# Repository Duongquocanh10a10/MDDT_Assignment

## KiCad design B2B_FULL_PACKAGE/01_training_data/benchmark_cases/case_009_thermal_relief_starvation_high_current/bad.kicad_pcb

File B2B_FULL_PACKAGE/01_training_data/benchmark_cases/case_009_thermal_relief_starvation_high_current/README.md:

# Benchmark Case: case_009_thermal_relief_starvation_high_current

## Title
High-Current Boost Inductor Pad Thermal Relief Starvation

## Category
`thermal_spoke_starvation` (IPC-2221 & IPC-7351 Standards)

## Engineering Description & Root Cause
MT3608 2.2A inductor switching node pad was connected to copper zone via only 1 of 4 spokes due to routing corridor choke, violating IPC-2221 current carrying capacity (0.8A max per spoke). Transformation reorients escape vias to restore all 4 0.40mm thermal spokes.

## Verification Metrics
- **Initial DRC Violations:** 2
- **Post-Transformation Violations:** 0 (100% Convergence Verified)
- **Signal Integrity Improvement:** Validated with open-source field solver models.

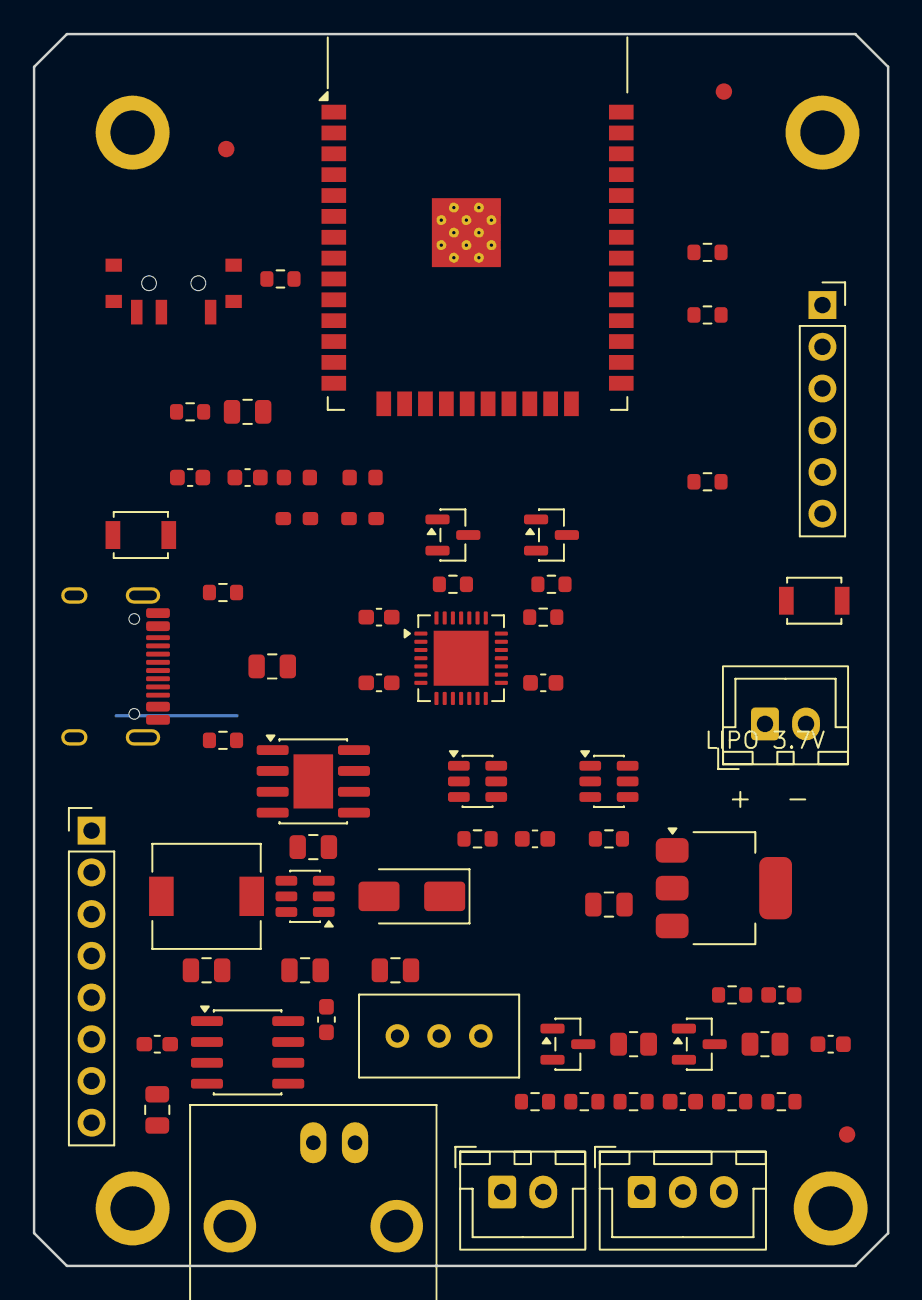
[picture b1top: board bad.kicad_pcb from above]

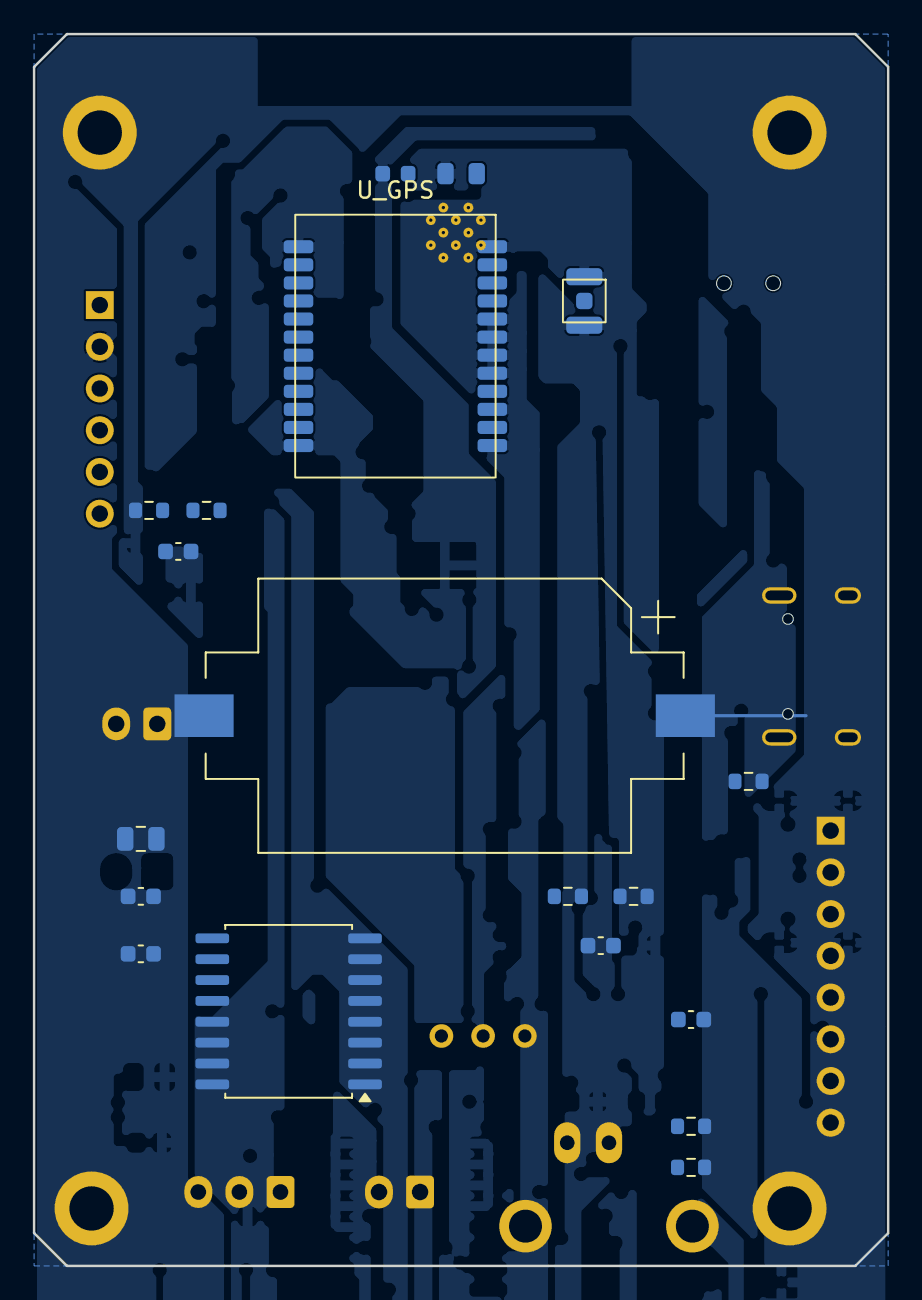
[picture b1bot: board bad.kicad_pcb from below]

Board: 4 copper layers, 52.0 x 75.0 mm, 94 parts (19 on the bottom side), 62 nets.

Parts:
BT1: CR2032; BatteryHolder_Keystone_1060_1x2032
C_ANA_BULK: 10uF; C_0805_2012Metric
C_BAT_ADC: 100nF; C_0603_1608Metric
C_BAT_CHG: 10uF; C_0805_2012Metric
C_BST_IN: 22uF; C_0805_2012Metric
C_BST_OUT1, C_BST_OUT2: 22uF; C_0805_2012Metric
C_CP_DEC: 100nF; C_0603_1608Metric
C_CP_VDD: 4.7uF; C_0603_1608Metric
C_CP_VREG: 4.7uF; C_0603_1608Metric
C_DS_VCC: 100nF; C_0603_1608Metric
C_EN: 100nF; C_0603_1608Metric
C_FF: 22pF; C_0603_1608Metric
C_GPS1: 100nF; C_0603_1608Metric
C_GPS2: 10uF; C_0805_2012Metric
C_LCD_VCC: 100nF; C_0603_1608Metric
C_LDO_DEC: 100nF; C_0603_1608Metric
C_LDO_IN: 10uF; C_0805_2012Metric
C_LDO_OUT: 22uF; C_0805_2012Metric
C_MCU_BULK: 10uF; C_0805_2012Metric
C_MCU_DEC: 100nF; C_0603_1608Metric
C_PH_FILT: 100nF; C_0603_1608Metric
C_RTC_VCC: 100nF; C_0603_1608Metric
C_TDS_FILT: 100nF; C_0603_1608Metric
C_U9_VCC: 100nF; C_0603_1608Metric
C_VBUS: 10uF; C_0805_2012Metric
C_VDD: 100nF; C_0603_1608Metric
D1: SS34; D_SMA
D_CHRG: CHRG; LED_0603_1608Metric
D_STDBY: STDBY; LED_0603_1608Metric
FB1: Ferrite_Bead; L_0603_1608Metric
FID1, FID2, FID3: FID; Fiducial_1mm_Mask2mm
H1, H2, H3, H4: M2.5; MountingHole_2.7mm_M2.5_Pad
J_ANT: U.FL; U.FL_Hirose_U.FL-R-SMT-1_Vertical
J_BAT: LIPO 3.7V; JST_XH_B2B-XH-A_1x02_P2.50mm_Vertical
J_BNC: BNC_pH; BNC_Amphenol_B6252HB-NPP3G-50_Horizontal
J_BOOT: BOOT/UART; PinHeader_1x06_P2.54mm_Vertical
J_LCD: TFT_LCD; PinHeader_1x08_P2.54mm_Vertical
J_TDS: TDS; JST_XH_B2B-XH-A_1x02_P2.50mm_Vertical
J_TEMP: DS18B20; JST_XH_B3B-XH-A_1x03_P2.50mm_Vertical
J_USB: USB-C; USB_C_Receptacle_HRO_TYPE-C-31-M-12
L1: 2.2uH; L_6.3x6.3_H3
Q1: 2N7002_TDS; SOT-23
Q2: 2N7002_LCD; SOT-23
Q3, Q4: MMBT3904; SOT-23
RV1: 10k_OFFSET; Potentiometer_Bourns_3296W_Vertical
R_BAT1, R_BAT2: 100k; R_0603_1608Metric
R_BL_LIM: 15R; R_0805_2012Metric
R_CC1, R_CC2: 5.1k; R_0603_1608Metric
R_CHRG: 1k; R_0603_1608Metric
R_CP_RST: 10k; R_0603_1608Metric
R_CS: 1k; R_0603_1608Metric
R_DS_PU: 4.7k; R_0603_1608Metric
R_DTR: 10k; R_0603_1608Metric
R_EN: 10k; R_0603_1608Metric
R_FB1: 22k; R_0603_1608Metric
R_FB2: 3.0k; R_0603_1608Metric
R_IO0: 10k; R_0603_1608Metric
R_LCD_GATE: 1k; R_0603_1608Metric
R_LCD_PD: 100k; R_0603_1608Metric
R_PH_BIAS: 10k; R_0603_1608Metric
R_PH_FILT: 1k; R_0603_1608Metric
R_PROG: 2.4k; R_0603_1608Metric
R_RTC_PU: 10k; R_0603_1608Metric
R_RTS: 10k; R_0603_1608Metric
R_SCL_PU: 4.7k; R_0603_1608Metric
R_SDA_PU: 4.7k; R_0603_1608Metric
R_STDBY: 1k; R_0603_1608Metric
R_TDS_FILT: 1k; R_0603_1608Metric
R_TDS_GATE: 1k; R_0603_1608Metric
R_TDS_PD: 100k; R_0603_1608Metric
R_TDS_REF: 1k_1%; R_0805_2012Metric
R_VDD: 100R; R_0603_1608Metric
SW1: ON/OFF; SW_SPDT_PCM12
SW_BOOT: BOOT; SW_SPST_B3U-1000P
SW_EN: RESET; SW_SPST_B3U-1000P
U1: TP4056; SOIC-8-1EP_3.9x4.9mm_P1.27mm_EP2.41x3.3mm
U2: DW01A; SOT-23-6
U3: FS8205A; SOT-23-6
U4: MT3608; SOT-23-6
U5: AMS1117; SOT-223-3_TabPin2
U6: ESP32; ESP32-WROOM-32
U7: DS3231; SOIC-16W_7.5x10.3mm_P1.27mm
U8: CP2102N; QFN-28-1EP_5x5mm_P0.5mm_EP3.35x3.35mm
U9: MCP6002; SOIC-8_3.9x4.9mm_P1.27mm
U_GPS: NEO-M8N; u-blox_NEO

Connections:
+3V3: C_DS_VCC.1, C_GPS1.1, C_GPS2.1, C_LCD_VCC.1, C_LDO_DEC.1, C_LDO_OUT.1, C_MCU_BULK.1, C_MCU_DEC.1, C_RTC_VCC.1, J_BOOT.1, J_LCD.2, J_TEMP.3, R_DS_PU.2, R_EN.2, R_IO0.2, R_RTC_PU.2, R_SCL_PU.2, R_SDA_PU.2, R_TDS_REF.2, U5.2, U6.2, U7.2, U_GPS.22, U_GPS.23
+5V: C_BST_OUT1.1, C_BST_OUT2.1, C_FF.1, C_LDO_IN.1, D1.1, FB1.1, R_FB1.1, U5.3
+5V_ANA: C_ANA_BULK.1, C_U9_VCC.1, FB1.2, RV1.1, U9.8
BAT_MONITOR: C_BAT_ADC.1, R_BAT1.2, R_BAT2.1, U6.5
BST_FB: C_FF.2, R_FB1.2, R_FB2.1, U4.3
B_MINUS: C_VDD.2, J_BAT.2, U2.6, U3.3
CC1: J_USB.A5, R_CC1.1
CC2: J_USB.B5, R_CC2.1
CHIP_PU: C_EN.1, J_BOOT.6, Q4.3, R_EN.1, SW_EN.1, U6.3
CHRG_ANODE: D_CHRG.2, R_CHRG.2
CHRG_LED: D_CHRG.1, U1.7
CP_DTR: Q4.2, R_DTR.1, U8.28
CP_RST: R_CP_RST.2, U8.9
CP_RTS: Q3.2, R_RTS.1, U8.24
CP_VDD: C_CP_DEC.1, C_CP_VDD.1, R_CP_RST.1, U8.6
DRAIN_U3: U3.1, U3.6
DW01_CS: R_CS.2, U2.2
DW01_VDD: C_VDD.1, R_VDD.2, U2.5
GND: BT1.2, C_ANA_BULK.2, C_BAT_ADC.2, C_BAT_CHG.2, C_BST_IN.2, C_BST_OUT1.2, C_BST_OUT2.2, C_CP_DEC.2, C_CP_VDD.2, C_CP_VREG.2, C_DS_VCC.2, C_EN.2, C_GPS1.2, C_GPS2.2, C_LCD_VCC.2, C_LDO_DEC.2, C_LDO_IN.2, C_LDO_OUT.2, C_MCU_BULK.2, C_MCU_DEC.2, C_PH_FILT.2, C_RTC_VCC.2, C_TDS_FILT.2, C_U9_VCC.2, C_VBUS.2, H1.1, H2.1, H3.1, H4.1, J_ANT.2, J_BOOT.2, J_LCD.1, J_TEMP.1, J_USB.A1, J_USB.A12, J_USB.B1, J_USB.B12, J_USB.SH, Q1.2, Q2.2, RV1.3, R_BAT2.2, R_CC1.2, R_CC2.2, R_CS.1, R_FB2.2, R_LCD_PD.2, R_PROG.2, R_TDS_PD.2, SW_BOOT.2, SW_EN.2, U1.1, U1.3, U1.9, U3.2, U4.2, U4.6, U5.1, U6.1, U6.15, U6.38, U6.39, U7.5, U7.6, U7.7, U7.8, U7.9, U7.10, U7.11, U7.12, U7.13, U8.3, U8.29, U9.4, U9.5, U_GPS.1, U_GPS.5, U_GPS.6, U_GPS.7, U_GPS.8, U_GPS.10, U_GPS.12, U_GPS.13, U_GPS.24
GPS_ANT: J_ANT.1, U_GPS.4
GPS_RX: U6.13, U_GPS.20
GPS_TX: U6.16, U_GPS.21
I2C_SCL: R_SCL_PU.1, U6.36, U7.16
I2C_SDA: R_SDA_PU.1, U6.33, U7.15
IO0: J_BOOT.5, Q3.3, R_IO0.1, SW_BOOT.1, U6.25
LCD_BL_PWM: R_LCD_GATE.1, U6.8
LCD_BL_SINK: Q2.3, R_BL_LIM.1
LCD_CS: J_LCD.7, U6.29
LCD_DC: J_LCD.6, U6.27
LCD_GATE: Q2.1, R_LCD_GATE.2, R_LCD_PD.1
LCD_LED_K: J_LCD.8, R_BL_LIM.2
LCD_RST: J_LCD.5, U6.28
LM358B_OUT: U9.6, U9.7
N_Q3_B: Q3.1, R_DTR.2
N_Q4_B: Q4.1, R_RTS.2
OC_GATE: U2.3, U3.4
OD_GATE: U2.1, U3.5
ONEWIRE_TEMP: J_TEMP.2, R_DS_PU.1, U6.26
PH_ADC: C_PH_FILT.1, R_PH_FILT.2, U6.6
PH_AMP_OUT: R_PH_FILT.1, U9.1, U9.2
PH_OFFSET: J_BNC.2, RV1.2, R_PH_BIAS.1
PH_SIGNAL: J_BNC.1, R_PH_BIAS.2, U9.3
RTC_INT: R_RTC_PU.1, U6.9, U7.3
RX0: J_BOOT.4, U6.34, U8.26
SPI_MOSI: J_LCD.4, U6.37
SPI_SCK: J_LCD.3, U6.30
STDBY_ANODE: D_STDBY.2, R_STDBY.2
STDBY_LED: D_STDBY.1, U1.6
SW_NODE: D1.2, L1.2, U4.1
TDS_ADC: C_TDS_FILT.1, R_TDS_FILT.2, U6.7
TDS_GATE: Q1.1, R_TDS_GATE.2, R_TDS_PD.1
TDS_PROBE_DRIVE: J_TDS.1, Q1.3
TDS_PWR_CTRL: R_TDS_GATE.1, U6.11
TDS_SENSE: J_TDS.2, R_TDS_FILT.1, R_TDS_REF.1
TX0: J_BOOT.3, U6.35, U8.25
U1_PROG: R_PROG.1, U1.2
USB_D+: J_USB.A6, J_USB.B6, U8.4
USB_D-: J_USB.A7, J_USB.B7, U8.5
VBAT_RAW: C_BAT_CHG.1, J_BAT.1, R_VDD.1, SW1.3, U1.5
VBAT_RTC: BT1.1, U7.14
VBAT_SW: C_BST_IN.1, L1.1, R_BAT1.1, SW1.2, U4.4, U4.5
VBUS: C_CP_VREG.1, C_VBUS.1, J_USB.A4, J_USB.A9, J_USB.B4, J_USB.B9, R_CHRG.1, R_STDBY.1, U1.4, U1.8, U8.7, U8.8
